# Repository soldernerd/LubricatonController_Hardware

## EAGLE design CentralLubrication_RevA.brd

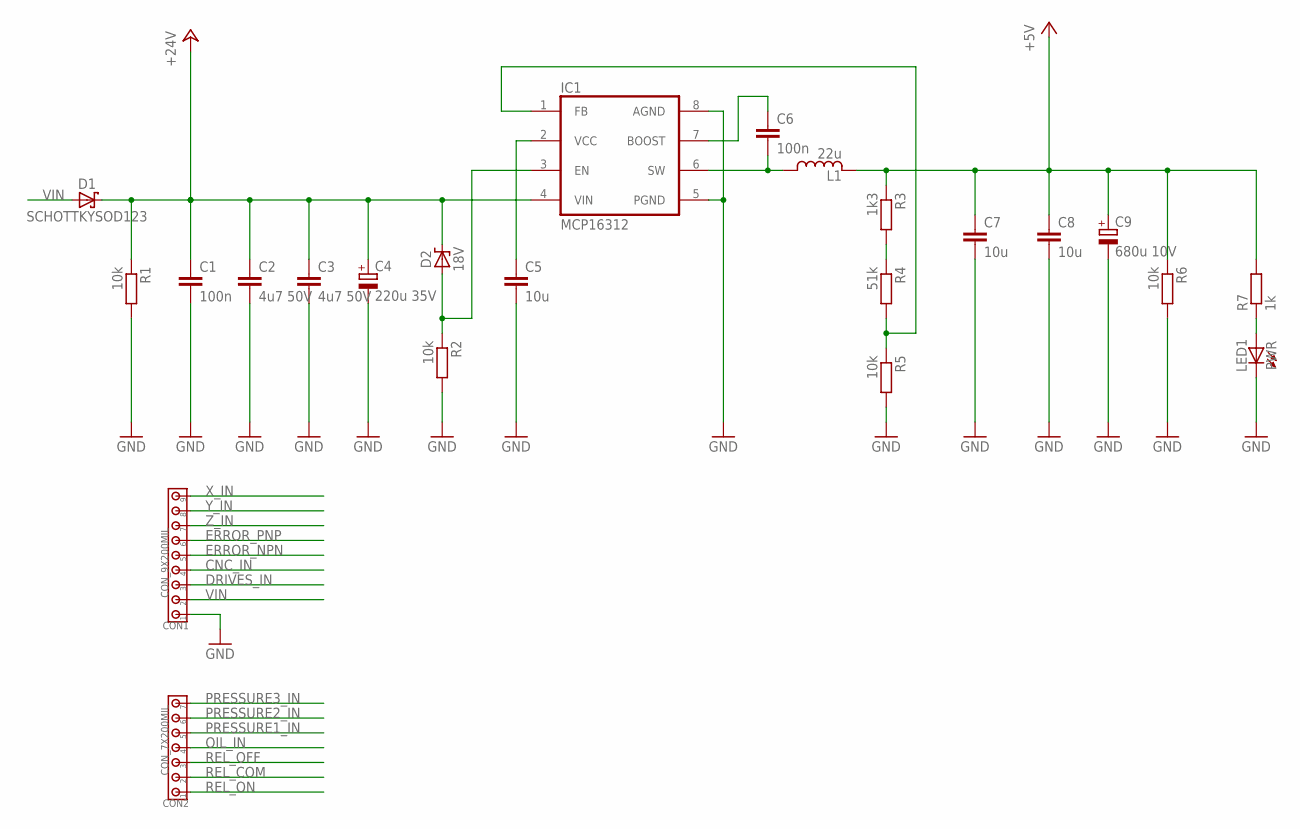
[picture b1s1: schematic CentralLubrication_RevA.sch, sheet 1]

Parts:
C1, C6: 100n; C0805
C2, C3: 4u7 50V; C1206
C4: 220u 35V; 8MM
C5, C7, C8: 10u; C0805
C9: 680u 10V; 8MM
CON1: CON_9X200MIL; 200MIL_9X
CON2: CON_7X200MIL; 200MIL_7X
D1: SCHOTTKYSOD123; SOD123
D2: 18V; SOD323
IC1: MCP16312; MSOP8
L1: 22u; LPS4018
LED1: PWR; LED0805_NOBOARDER
R1, R2, R5, R6: 10k; R0805
R3: 1k3; R0805
R4: 51k; R0805
R7: 1k; R0805

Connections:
+5V: C7.1, C8.1, C9.+, L1.2, R3.1, R6.1, R7.2; also elsewhere on the board
+24V: C1.1, C2.1, C3.1, C4.+, D1.C, D2.C, IC1.4 (VIN), R1.1; also elsewhere on the board
BOOST: C6.1, IC1.7 (BOOST)
CNC_IN: CON1.4; also elsewhere on the board
DRIVES_IN: CON1.3; also elsewhere on the board
ERROR_NPN: CON1.5; also elsewhere on the board
ERROR_PNP: CON1.6; also elsewhere on the board
GND: C1.2, C2.2, C3.2, C4.-, C5.2, C7.2, C8.2, C9.-, CON1.1, IC1.5 (PGND), IC1.8 (AGND), LED1.C, R1.2, R2.2, R5.2, R6.2; also elsewhere on the board
unnamed: IC1.1 (FB), R4.2, R5.1
unnamed: R3.2, R4.1
unnamed: C5.1, IC1.2 (VCC)
unnamed: D2.A, IC1.3 (EN), R2.1
unnamed: LED1.A, R7.1
OIL_IN: CON2.4; also elsewhere on the board
PRESSURE1_IN: CON2.5; also elsewhere on the board
PRESSURE2_IN: CON2.6; also elsewhere on the board
PRESSURE3_IN: CON2.7; also elsewhere on the board
REL_COM: CON2.2; also elsewhere on the board
REL_OFF: CON2.3; also elsewhere on the board
REL_ON: CON2.1; also elsewhere on the board
SWITCH1: C6.2, IC1.6 (SW), L1.1
VIN: CON1.2, D1.A
X_IN: CON1.9; also elsewhere on the board
Y_IN: CON1.8; also elsewhere on the board
Z_IN: CON1.7; also elsewhere on the board

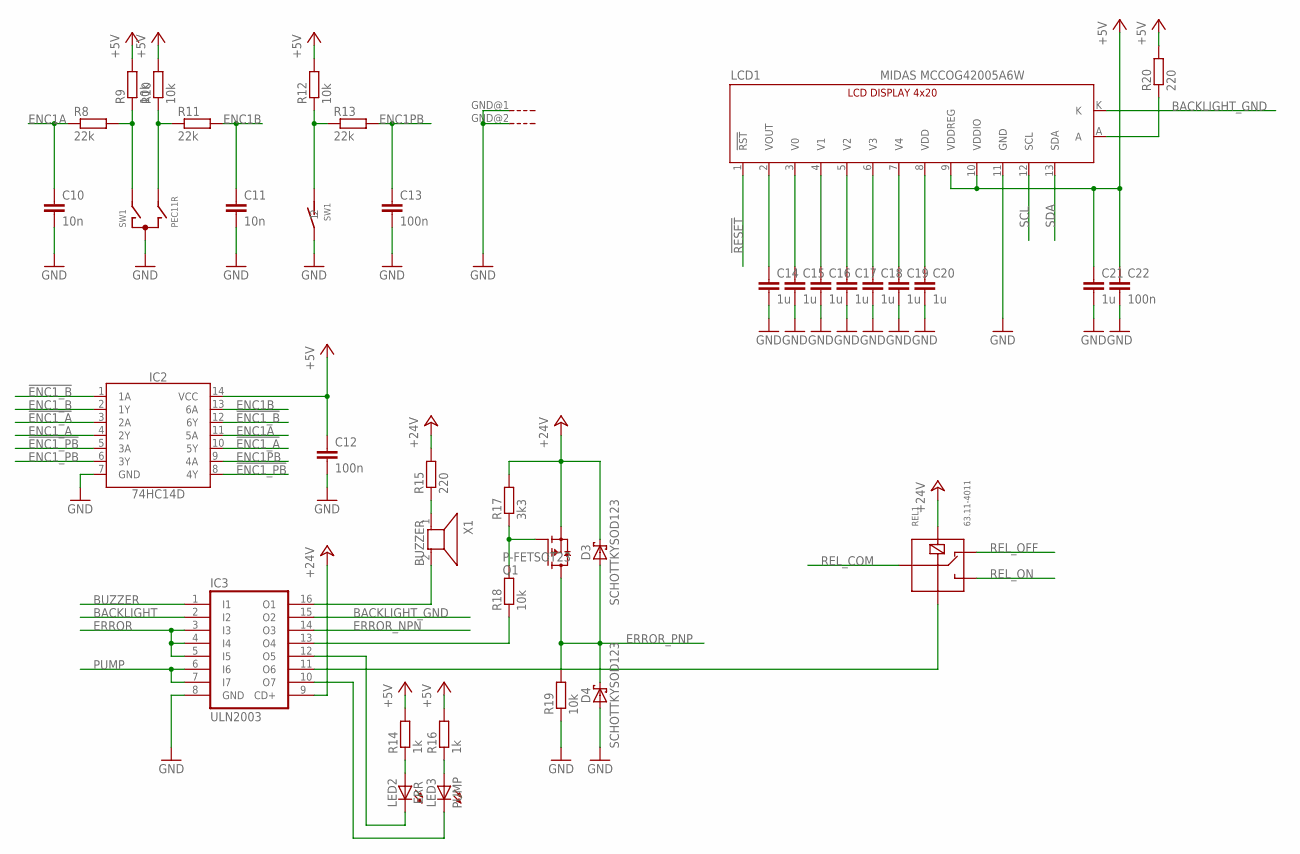
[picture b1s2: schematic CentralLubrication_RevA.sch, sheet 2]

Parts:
C10, C11: 10n; C0805
C12, C13, C22: 100n; C0805
C14, C15, C16, C17, C18, C19, C20, C21: 1u; C0805
D3, D4: SCHOTTKYSOD123; SOD123
IC2: 74HC14D; SO14
IC3: ULN2003; SO16
LCD1: MIDAS MCCOG42005A6W; LCD_4X20_I2C
LED2: ERR; LED0805_NOBOARDER
LED3: PUMP; LED0805_NOBOARDER
Q1: P-FETSOT23; SOT23
R8, R11, R13: 22k; R0805
R9, R10, R12, R18, R19: 10k; R0805
R14, R16: 1k; R0805
R15, R20: 220; R0805
R17: 3k3; R0805
REL1: 63.11-4011; G5LE
SW1: PEC11R; ENCODER_BOURNS
X1: BUZZER; BUZZER_14MM

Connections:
!ENC1_A!: IC2.3 (2A), IC2.10 (5Y)
!ENC1_B!: IC2.1 (1A), IC2.12 (6Y)
!ENC1_PB!: IC2.5 (3A), IC2.8 (4Y)
!RESET!: LCD1.1 (!RST!); also elsewhere on the board
+5V: C12.1, C21.1, C22.1, IC2.14 (VCC), LCD1.9 (VDDREG), LCD1.10 (VDDIO), R9.2, R10.2, R12.2, R14.2, R16.2, R20.2; also elsewhere on the board
+24V: D3.C, IC3.9 (CD+), Q1.2 (S), R15.2, R17.2, REL1.2; also elsewhere on the board
BACKLIGHT: IC3.2 (I2); also elsewhere on the board
BACKLIGHT_GND: IC3.15 (O2), LCD1.K
BUZZER: IC3.1 (I1); also elsewhere on the board
BUZZER_GND: IC3.16 (O1), X1.2
ENC1A: C10.1, IC2.11 (5A), R8.1
ENC1B: C11.1, IC2.13 (6A), R11.2
ENC1PB: C13.1, IC2.9 (4A), R13.2
ENC1_A: IC2.4 (2Y); also elsewhere on the board
ENC1_B: IC2.2 (1Y); also elsewhere on the board
ENC1_PB: IC2.6 (3Y); also elsewhere on the board
ERROR: IC3.3 (I3), IC3.4 (I4), IC3.5 (I5); also elsewhere on the board
ERROR_NPN: IC3.14 (O3); also elsewhere on the board
ERROR_PNP: D3.A, D4.C, Q1.3 (D), R19.2; also elsewhere on the board
GND: C10.2, C11.2, C12.2, C13.2, C14.2, C15.2, C16.2, C17.2, C18.2, C19.2, C20.2, C21.2, C22.2, D4.A, IC2.7 (GND), IC3.8 (GND), LCD1.11 (GND), R19.1, SW1.2, SW1.C, SW1.GND@1 (G), SW1.GND@2 (G); also elsewhere on the board
unnamed: C20.1, LCD1.8 (VDD)
unnamed: R15.1, X1.1
unnamed: R10.1, R11.1, SW1.B
unnamed: R8.2, R9.1, SW1.A
unnamed: LCD1.A, R20.1
unnamed: IC3.11 (O6), REL1.1
unnamed: Q1.1 (G), R17.1, R18.2
unnamed: R12.1, R13.1, SW1.1
unnamed: IC3.13 (O4), R18.1
unnamed: C14.1, LCD1.2 (VOUT)
unnamed: C15.1, LCD1.3 (V0)
unnamed: C19.1, LCD1.7 (V4)
unnamed: C18.1, LCD1.6 (V3)
unnamed: C17.1, LCD1.5 (V2)
unnamed: C16.1, LCD1.4 (V1)
unnamed: IC3.10 (O7), LED3.C
unnamed: LED2.A, R14.1
unnamed: LED3.A, R16.1
unnamed: IC3.12 (O5), LED2.C
PUMP: IC3.6 (I6), IC3.7 (I7); also elsewhere on the board
REL_COM: REL1.COM; also elsewhere on the board
REL_OFF: REL1.O; also elsewhere on the board
REL_ON: REL1.C; also elsewhere on the board
SCL: LCD1.12 (SCL); also elsewhere on the board
SDA: LCD1.13 (SDA); also elsewhere on the board

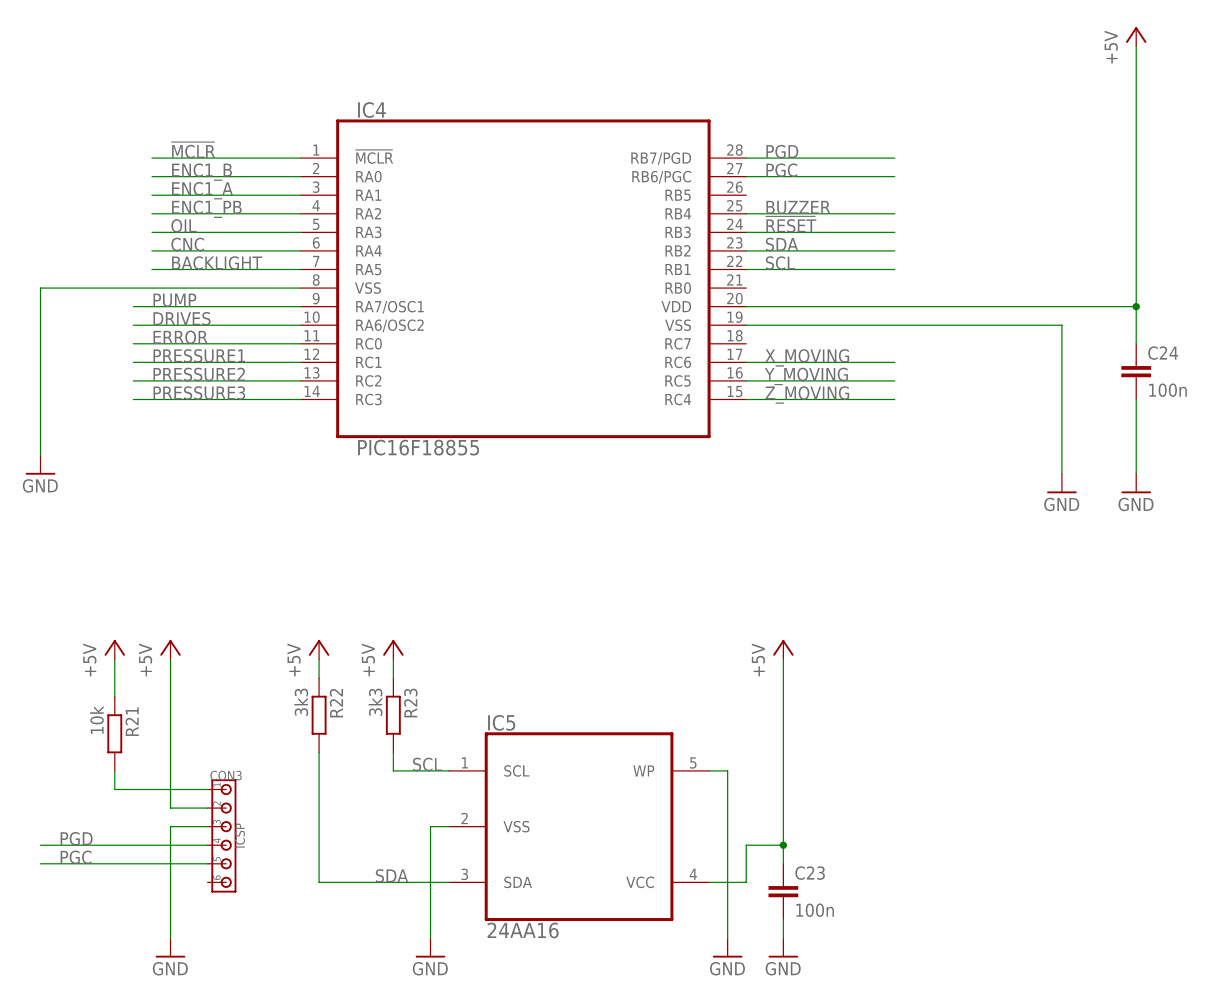
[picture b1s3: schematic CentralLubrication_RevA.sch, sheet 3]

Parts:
C23, C24: 100n; C0805
CON3: ICSP; 100MIL_6X
IC4: PIC16F18855; SO28W
IC5: 24AA16; SOT-23-5
R21: 10k; R0805
R22, R23: 3k3; R0805

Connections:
!MCLR!: CON3.1, IC4.1 (!MCLR!), R21.2
!RESET!: IC4.24 (RB3); also elsewhere on the board
+5V: C23.1, C24.1, CON3.2, IC4.20 (VDD), IC5.4 (VCC), R21.1, R22.1, R23.1; also elsewhere on the board
BACKLIGHT: IC4.7 (RA5); also elsewhere on the board
BUZZER: IC4.25 (RB4); also elsewhere on the board
CNC: IC4.6 (RA4); also elsewhere on the board
DRIVES: IC4.10 (RA6/OSC2); also elsewhere on the board
ENC1_A: IC4.3 (RA1); also elsewhere on the board
ENC1_B: IC4.2 (RA0); also elsewhere on the board
ENC1_PB: IC4.4 (RA2); also elsewhere on the board
ERROR: IC4.11 (RC0); also elsewhere on the board
GND: C23.2, C24.2, CON3.3, IC4.8 (VSS), IC4.19 (VSS), IC5.2 (VSS), IC5.5 (WP); also elsewhere on the board
OIL: IC4.5 (RA3); also elsewhere on the board
PGC: CON3.5, IC4.27 (RB6/PGC)
PGD: CON3.4, IC4.28 (RB7/PGD)
PRESSURE1: IC4.12 (RC1); also elsewhere on the board
PRESSURE2: IC4.13 (RC2); also elsewhere on the board
PRESSURE3: IC4.14 (RC3); also elsewhere on the board
PUMP: IC4.9 (RA7/OSC1); also elsewhere on the board
SCL: IC4.22 (RB1), IC5.1 (SCL), R23.2; also elsewhere on the board
SDA: IC4.23 (RB2), IC5.3 (SDA), R22.2; also elsewhere on the board
X_MOVING: IC4.17 (RC6); also elsewhere on the board
Y_MOVING: IC4.16 (RC5); also elsewhere on the board
Z_MOVING: IC4.15 (RC4); also elsewhere on the board

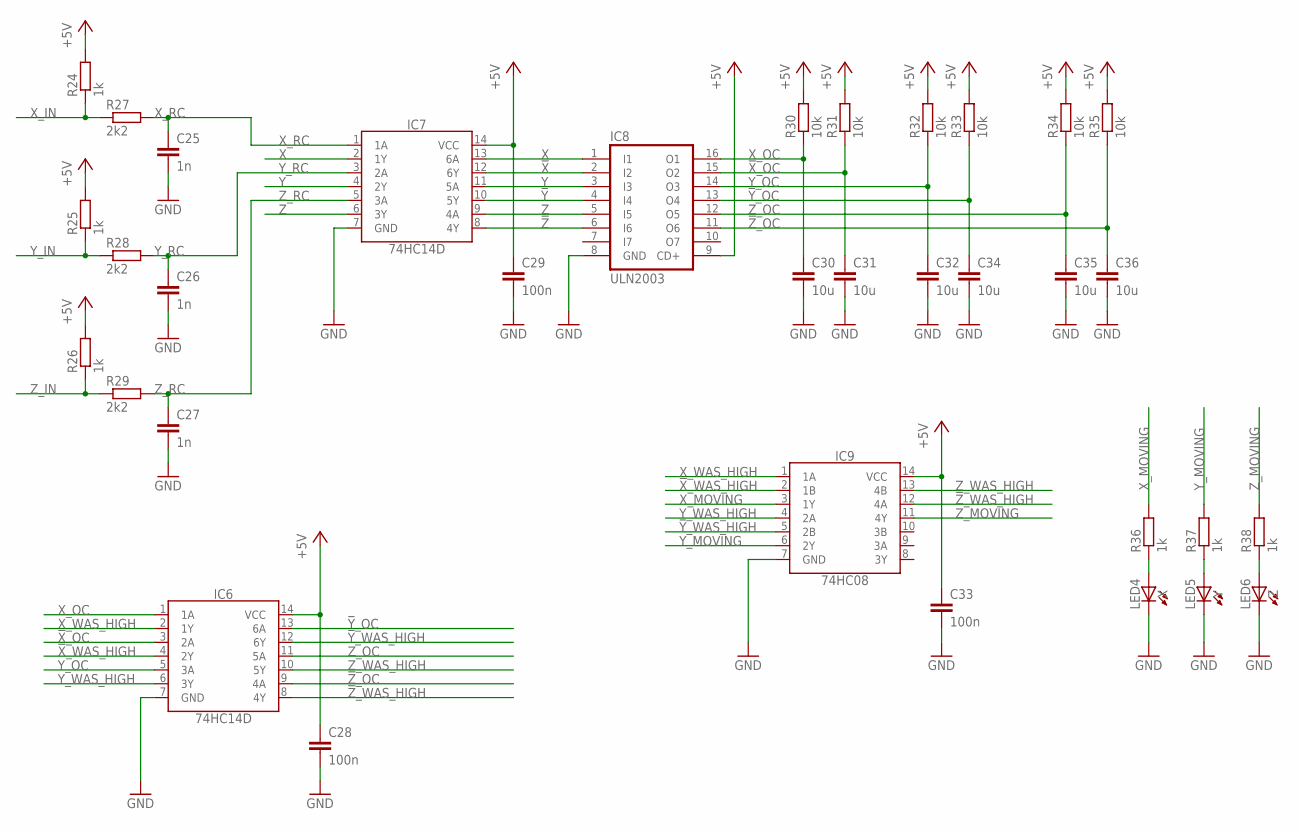
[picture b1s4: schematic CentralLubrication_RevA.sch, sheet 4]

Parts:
C25, C26, C27: 1n; C0805
C28, C29, C33: 100n; C0805
C30, C31, C32, C34, C35, C36: 10u; C0805
IC6, IC7: 74HC14D; SO14
IC8: ULN2003; SO16
IC9: 74HC08; SO14
LED4: X; LED0805_NOBOARDER
LED5: Y; LED0805_NOBOARDER
LED6: Z; LED0805_NOBOARDER
R24, R25, R26, R36, R37, R38: 1k; R0805
R27, R28, R29: 2k2; R0805
R30, R31, R32, R33, R34, R35: 10k; R0805

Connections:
!X!: IC7.12 (6Y), IC8.2 (I2)
!X!_OC: C31.1, IC6.3 (2A), IC8.15 (O2), R31.1
!X!_WAS_HIGH: IC6.4 (2Y), IC9.2 (1B)
!Y!: IC7.10 (5Y), IC8.4 (I4)
!Y!_OC: C34.1, IC6.13 (6A), IC8.13 (O4), R33.1
!Y!_WAS_HIGH: IC6.12 (6Y), IC9.5 (2B)
!Z!: IC7.8 (4Y), IC8.6 (I6)
!Z!_OC: C36.1, IC6.9 (4A), IC8.11 (O6), R35.1
!Z!_WAS_HIGH: IC6.8 (4Y), IC9.12 (4A)
+5V: C28.1, C29.1, C33.1, IC6.14 (VCC), IC7.14 (VCC), IC8.9 (CD+), IC9.14 (VCC), R24.2, R25.2, R26.2, R30.2, R31.2, R32.2, R33.2, R34.2, R35.2; also elsewhere on the board
GND: C25.2, C26.2, C27.2, C28.2, C29.2, C30.2, C31.2, C32.2, C33.2, C34.2, C35.2, C36.2, IC6.7 (GND), IC7.7 (GND), IC8.8 (GND), IC9.7 (GND), LED4.C, LED5.C, LED6.C; also elsewhere on the board
unnamed: LED4.A, R36.1
unnamed: LED5.A, R37.1
unnamed: LED6.A, R38.1
X: IC7.2 (1Y), IC7.13 (6A), IC8.1 (I1)
X_IN: R24.1, R27.1; also elsewhere on the board
X_MOVING: IC9.3 (1Y), R36.2; also elsewhere on the board
X_OC: C30.1, IC6.1 (1A), IC8.16 (O1), R30.1
X_RC: C25.1, IC7.1 (1A), R27.2
X_WAS_HIGH: IC6.2 (1Y), IC9.1 (1A)
Y: IC7.4 (2Y), IC7.11 (5A), IC8.3 (I3)
Y_IN: R25.1, R28.1; also elsewhere on the board
Y_MOVING: IC9.6 (2Y), R37.2; also elsewhere on the board
Y_OC: C32.1, IC6.5 (3A), IC8.14 (O3), R32.1
Y_RC: C26.1, IC7.3 (2A), R28.2
Y_WAS_HIGH: IC6.6 (3Y), IC9.4 (2A)
Z: IC7.6 (3Y), IC7.9 (4A), IC8.5 (I5)
Z_IN: R26.1, R29.1; also elsewhere on the board
Z_MOVING: IC9.11 (4Y), R38.2; also elsewhere on the board
Z_OC: C35.1, IC6.11 (5A), IC8.12 (O5), R34.1
Z_RC: C27.1, IC7.5 (3A), R29.2
Z_WAS_HIGH: IC6.10 (5Y), IC9.13 (4B)

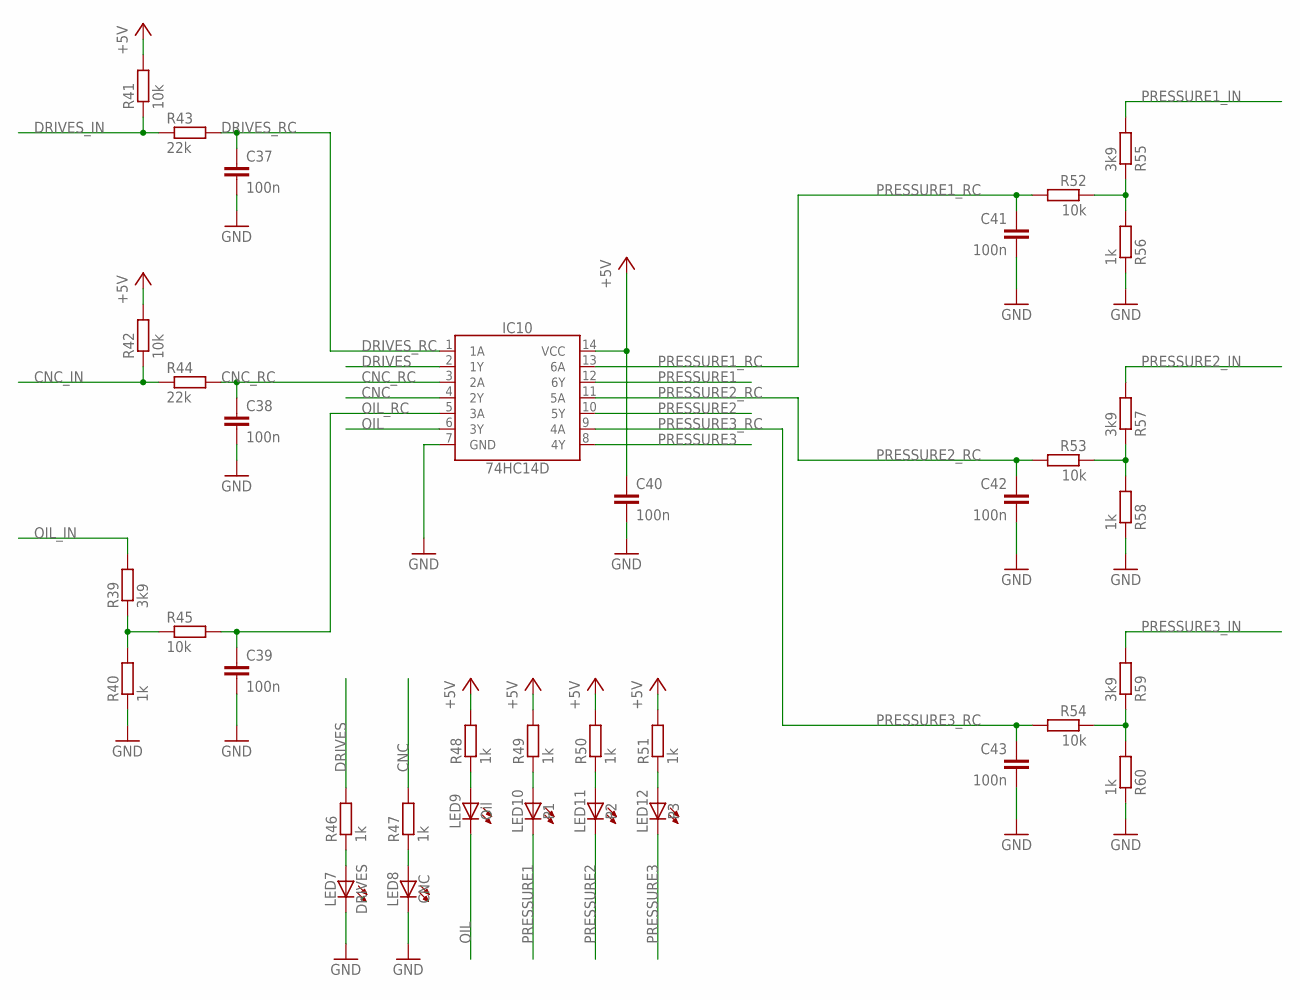
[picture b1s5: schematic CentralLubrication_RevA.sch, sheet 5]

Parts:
C37, C38, C39, C40, C41, C42, C43: 100n; C0805
IC10: 74HC14D; SO14
LED7: DRIVES; LED0805_NOBOARDER
LED8: CNC; LED0805_NOBOARDER
LED9: Oil; LED0805_NOBOARDER
LED10: P1; LED0805_NOBOARDER
LED11: P2; LED0805_NOBOARDER
LED12: P3; LED0805_NOBOARDER
R39, R55, R57, R59: 3k9; R0805
R40, R46, R47, R48, R49, R50, R51, R56, R58, R60: 1k; R0805
R41, R42, R45, R52, R53, R54: 10k; R0805
R43, R44: 22k; R0805

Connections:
+5V: C40.1, IC10.14 (VCC), R41.2, R42.2, R48.2, R49.2, R50.2, R51.2; also elsewhere on the board
CNC: IC10.4 (2Y), R47.2; also elsewhere on the board
CNC_IN: R42.1, R44.1; also elsewhere on the board
CNC_RC: C38.1, IC10.3 (2A), R44.2
DRIVES: IC10.2 (1Y), R46.2; also elsewhere on the board
DRIVES_IN: R41.1, R43.1; also elsewhere on the board
DRIVES_RC: C37.1, IC10.1 (1A), R43.2
GND: C37.2, C38.2, C39.2, C40.2, C41.2, C42.2, C43.2, IC10.7 (GND), LED7.C, LED8.C, R40.1, R56.1, R58.1, R60.1; also elsewhere on the board
unnamed: R39.1, R40.2, R45.1
unnamed: R52.1, R55.1, R56.2
unnamed: R53.1, R57.1, R58.2
unnamed: R54.1, R59.1, R60.2
unnamed: LED7.A, R46.1
unnamed: LED8.A, R47.1
unnamed: LED9.A, R48.1
unnamed: LED10.A, R49.1
unnamed: LED11.A, R50.1
unnamed: LED12.A, R51.1
OIL: IC10.6 (3Y), LED9.C; also elsewhere on the board
OIL_IN: R39.2; also elsewhere on the board
OIL_RC: C39.1, IC10.5 (3A), R45.2
PRESSURE1: IC10.12 (6Y), LED10.C; also elsewhere on the board
PRESSURE1_IN: R55.2; also elsewhere on the board
PRESSURE1_RC: C41.1, IC10.13 (6A), R52.2
PRESSURE2: IC10.10 (5Y), LED11.C; also elsewhere on the board
PRESSURE2_IN: R57.2; also elsewhere on the board
PRESSURE2_RC: C42.1, IC10.11 (5A), R53.2
PRESSURE3: IC10.8 (4Y), LED12.C; also elsewhere on the board
PRESSURE3_IN: R59.2; also elsewhere on the board
PRESSURE3_RC: C43.1, IC10.9 (4A), R54.2

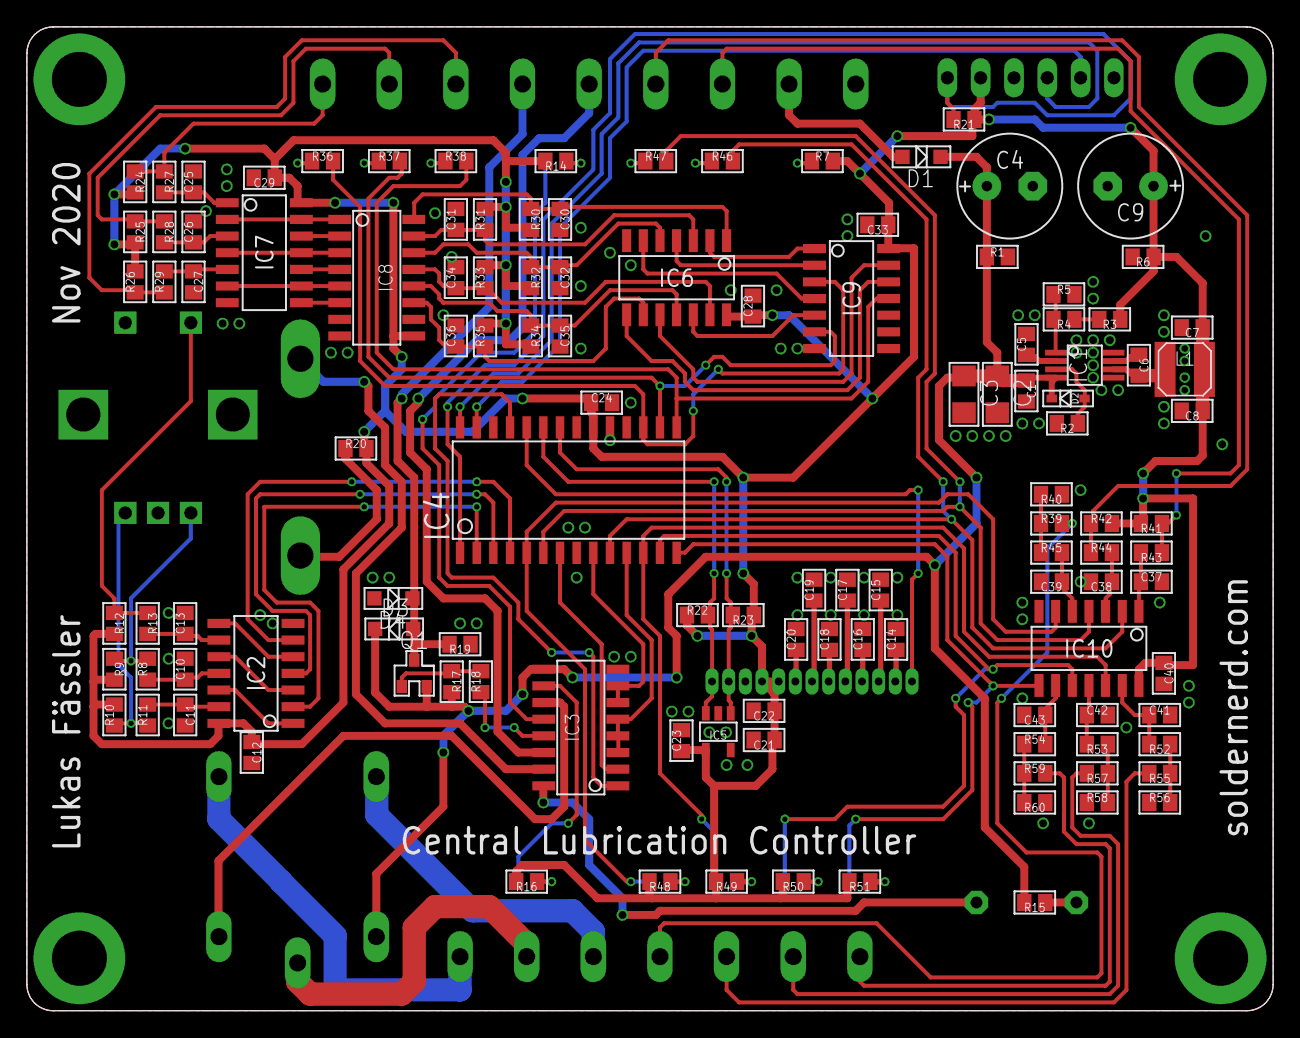
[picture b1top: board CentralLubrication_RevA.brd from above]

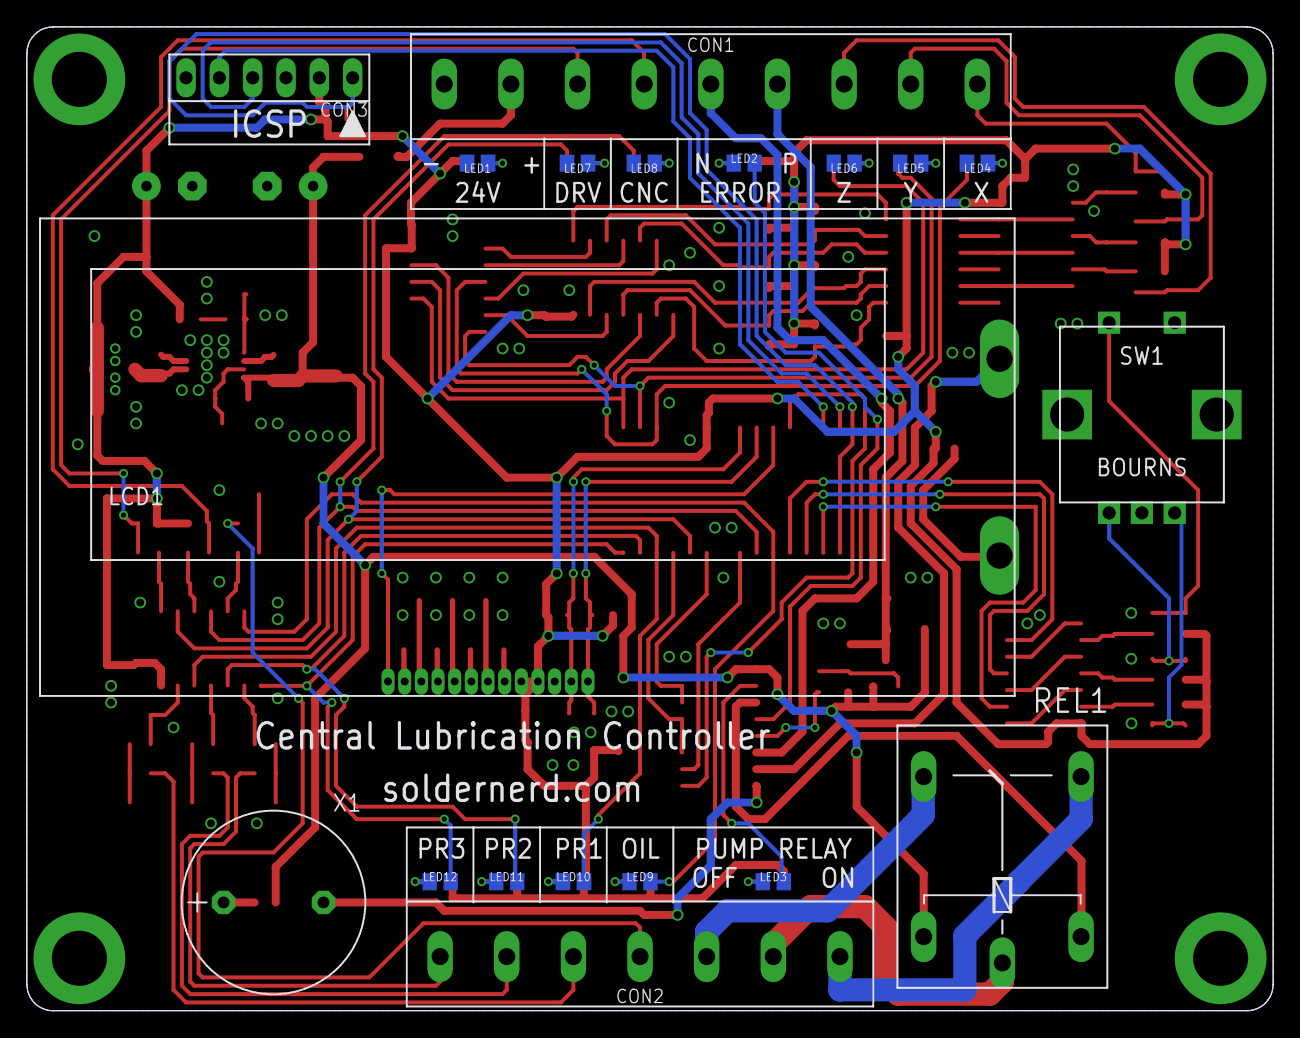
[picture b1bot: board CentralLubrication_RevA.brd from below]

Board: 2 copper layers, 95.0 x 75.0 mm, 138 parts (19 on the bottom side), 114 nets.

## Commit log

2020-12-08 Initial commit but presumably fully functional
